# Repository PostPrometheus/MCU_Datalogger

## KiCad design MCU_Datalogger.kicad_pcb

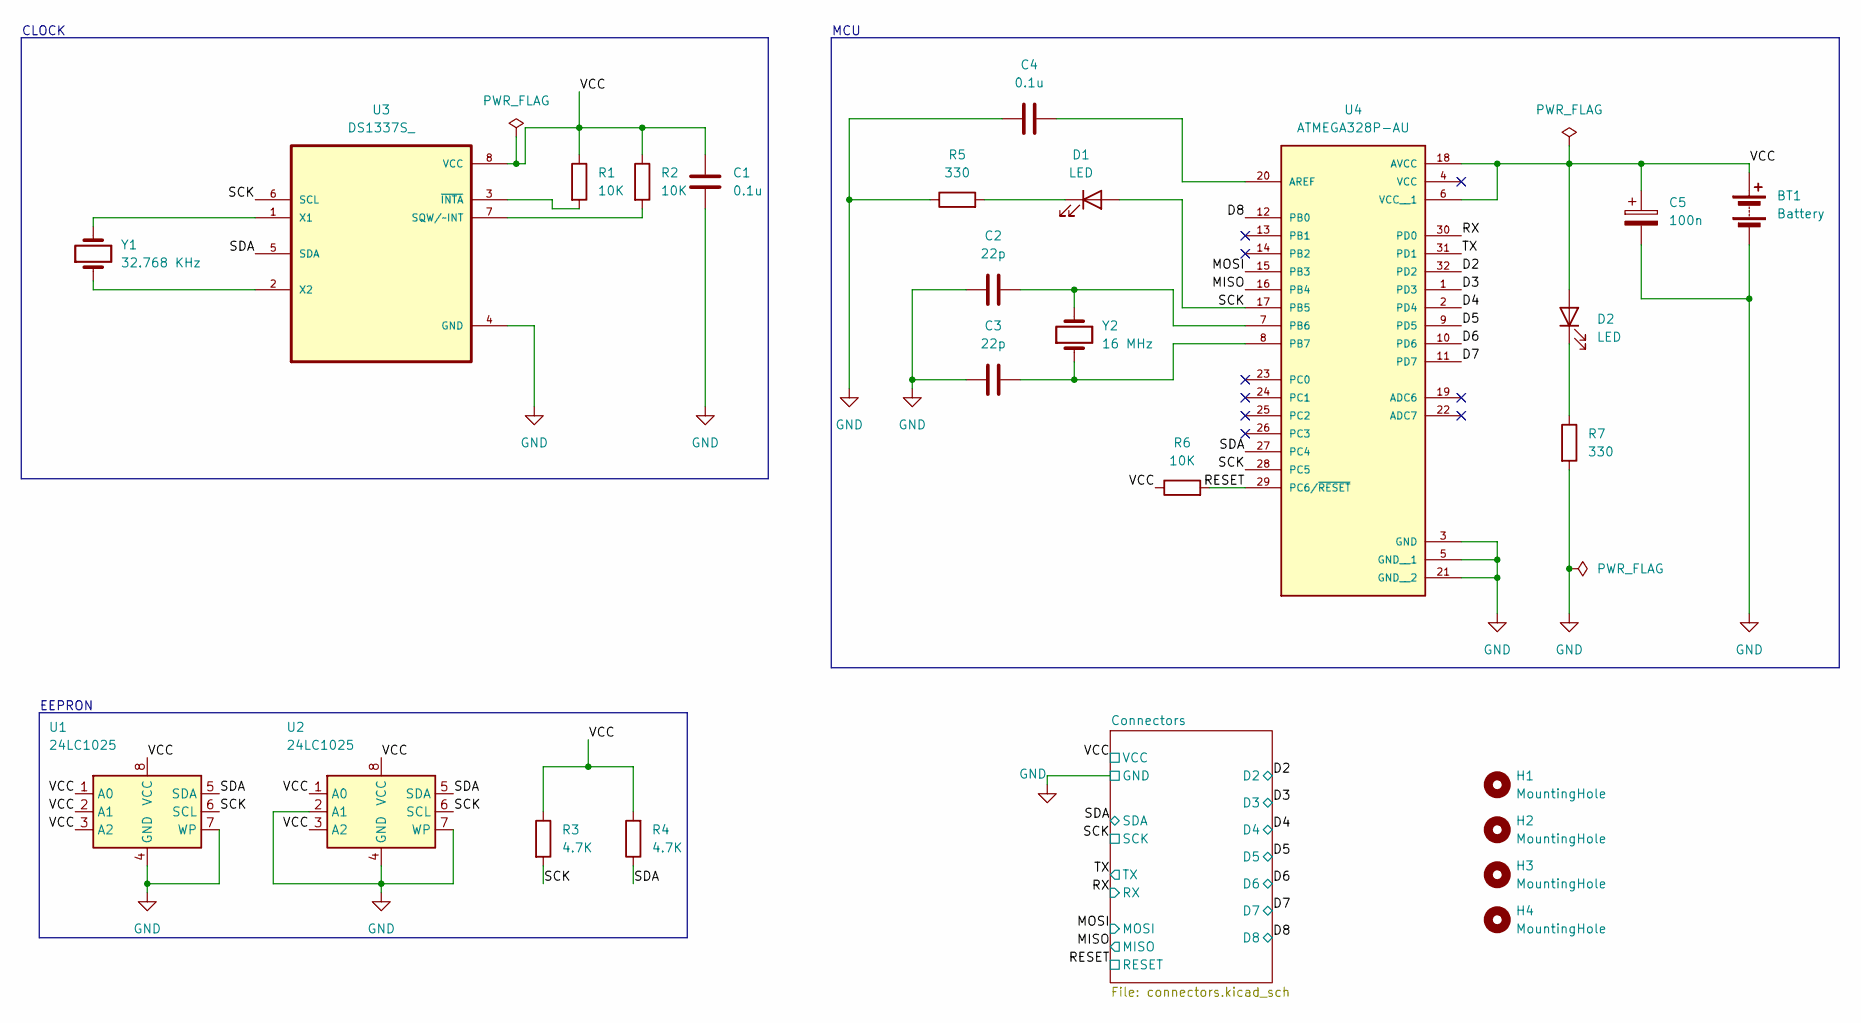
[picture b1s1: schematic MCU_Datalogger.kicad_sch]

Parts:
BT1: Battery; PinHeader_1x02_P2.54mm_Vertical
C1, C4: 0.1u; C_0805_2012Metric_Pad1.18x1.45mm_HandSolder
C2, C3: 22p; C_0805_2012Metric_Pad1.18x1.45mm_HandSolder
C5: 100n; C_0805_2012Metric_Pad1.18x1.45mm_HandSolder
D1, D2: LED; LED_0805_2012Metric_Pad1.15x1.40mm_HandSolder
H1, H2, H3, H4: MountingHole; MountingHole_2.1mm
R1, R2, R6: 10K; R_0805_2012Metric_Pad1.20x1.40mm_HandSolder
R3, R4: 4.7K; R_0805_2012Metric_Pad1.20x1.40mm_HandSolder
R5, R7: 330; R_0805_2012Metric_Pad1.20x1.40mm_HandSolder
U1, U2: 24LC1025; SOIC-8_5.3x5.3mm_P1.27mm
U3: DS1337S_; SOIC127P600X175-8N
U4: ATMEGA328P-AU; QFP80P900X900X120-32N; PARTREV 8271A; DigiKey_Part_Number ATMEGA328P-AU-ND
Y1: 32.768 KHz; Crystal_SMD_5032-2Pin_5.0x3.2mm_HandSoldering
Y2: 16 MHz; Crystal_SMD_5032-2Pin_5.0x3.2mm_HandSoldering

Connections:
/D2: U4.32 (PD2); also elsewhere on the board
/D3: U4.1 (PD3); also elsewhere on the board
/D4: U4.2 (PD4); also elsewhere on the board
/D5: U4.9 (PD5); also elsewhere on the board
/D6: U4.10 (PD6); also elsewhere on the board
/D7: U4.11 (PD7); also elsewhere on the board
/D8: U4.12 (PB0); also elsewhere on the board
/MISO: U4.16 (PB4); also elsewhere on the board
/MOSI: U4.15 (PB3); also elsewhere on the board
/RESET: R6.2, U4.29 (PC6/~RESET); also elsewhere on the board
/RX: U4.30 (PD0); also elsewhere on the board
/SCK: D1.2 (A), R3.2, U1.6 (SCL), U2.6 (SCL), U3.6 (SCL), U4.17 (PB5), U4.28 (PC5); also elsewhere on the board
/SDA: R4.1, U1.5 (SDA), U2.5 (SDA), U3.5 (SDA), U4.27 (PC4); also elsewhere on the board
/TX: U4.31 (PD1); also elsewhere on the board
/VCC: BT1.1 (+), C1.1, C5.1, D2.2 (A), R1.1, R2.1, R3.1, R4.2, R6.1, U1.1 (A0), U1.2 (A1), U1.3 (A2), U1.8 (VCC), U2.1 (A0), U2.3 (A2), U2.8 (VCC), U3.8 (VCC), U4.6 (VCC__1), U4.18 (AVCC); also elsewhere on the board
GND: BT1.2 (-), C1.2, C2.2, C3.1, C4.1, C5.2, R5.1, R7.2, U1.4 (GND), U1.7 (WP), U2.2 (A1), U2.4 (GND), U2.7 (WP), U3.4 (GND), U4.3 (GND), U4.5 (GND__1), U4.21 (GND__2); also elsewhere on the board
unnamed: D1.1 (K), R5.2
unnamed: D2.1 (K), R7.1
unnamed: R2.2, U3.7 (SQW/~INT)
unnamed: U3.1 (X1), Y1.2
unnamed: U3.2 (X2), Y1.1
unnamed: R1.2, U3.3 (~INTA)
unnamed: C4.2, U4.20 (AREF)
unnamed: C2.1, U4.7 (PB6), Y2.2
unnamed: C3.2, U4.8 (PB7), Y2.1

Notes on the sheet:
EEPRON
CLOCK
MCU

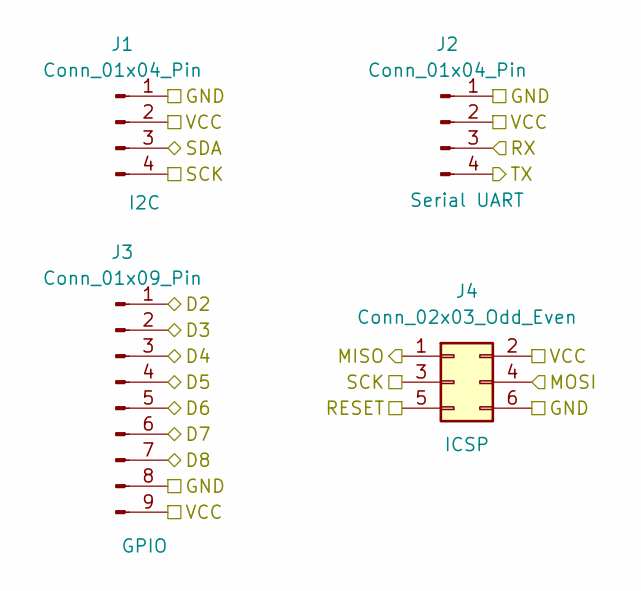
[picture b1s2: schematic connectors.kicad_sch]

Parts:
J1, J2: Conn_01x04_Pin; PinHeader_1x04_P2.54mm_Vertical
J3: Conn_01x09_Pin; PinHeader_1x09_P2.54mm_Vertical
J4: Conn_02x03_Odd_Even; PinHeader_2x03_P2.54mm_Vertical

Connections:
/D2: J3.1; also elsewhere on the board
/D3: J3.2; also elsewhere on the board
/D4: J3.3; also elsewhere on the board
/D5: J3.4; also elsewhere on the board
/D6: J3.5; also elsewhere on the board
/D7: J3.6; also elsewhere on the board
/D8: J3.7; also elsewhere on the board
/MISO: J4.1; also elsewhere on the board
/MOSI: J4.4; also elsewhere on the board
/RESET: J4.5; also elsewhere on the board
/RX: J2.3; also elsewhere on the board
/SCK: J1.4, J4.3; also elsewhere on the board
/SDA: J1.3; also elsewhere on the board
/TX: J2.4; also elsewhere on the board
/VCC: J1.2, J2.2, J3.9, J4.2; also elsewhere on the board
GND: J1.1, J2.1, J3.8, J4.6; also elsewhere on the board

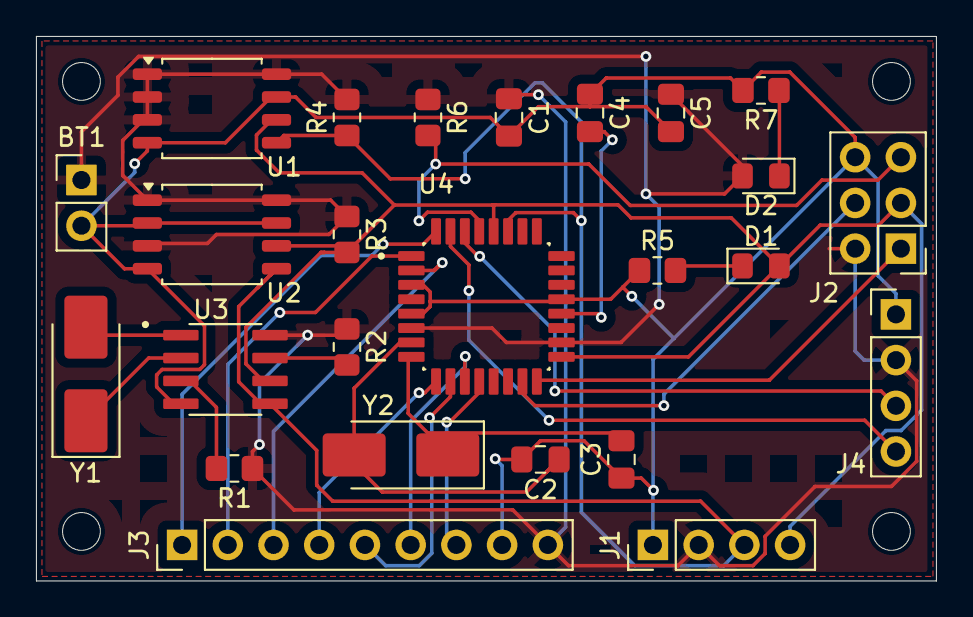
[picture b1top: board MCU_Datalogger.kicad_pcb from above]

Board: 2 copper layers, 50.0 x 30.2 mm, 29 parts (0 on the bottom side), 25 nets.

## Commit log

2025-08-28 chore: add .gitignore for KiCad
2025-08-28 Symbols
2025-08-28 Values
2025-08-28 Footprints
2025-08-28 Wiring Main
2025-08-28 Wiring
2025-08-28 Shematic Done
2025-08-28 Rout
2025-08-29 Completed 2-layer
2025-08-29 Solved Wire
2025-08-29 chore: update .gitignore to ignore Gerber outputs
2025-08-29 chore: update .gitignore rules
